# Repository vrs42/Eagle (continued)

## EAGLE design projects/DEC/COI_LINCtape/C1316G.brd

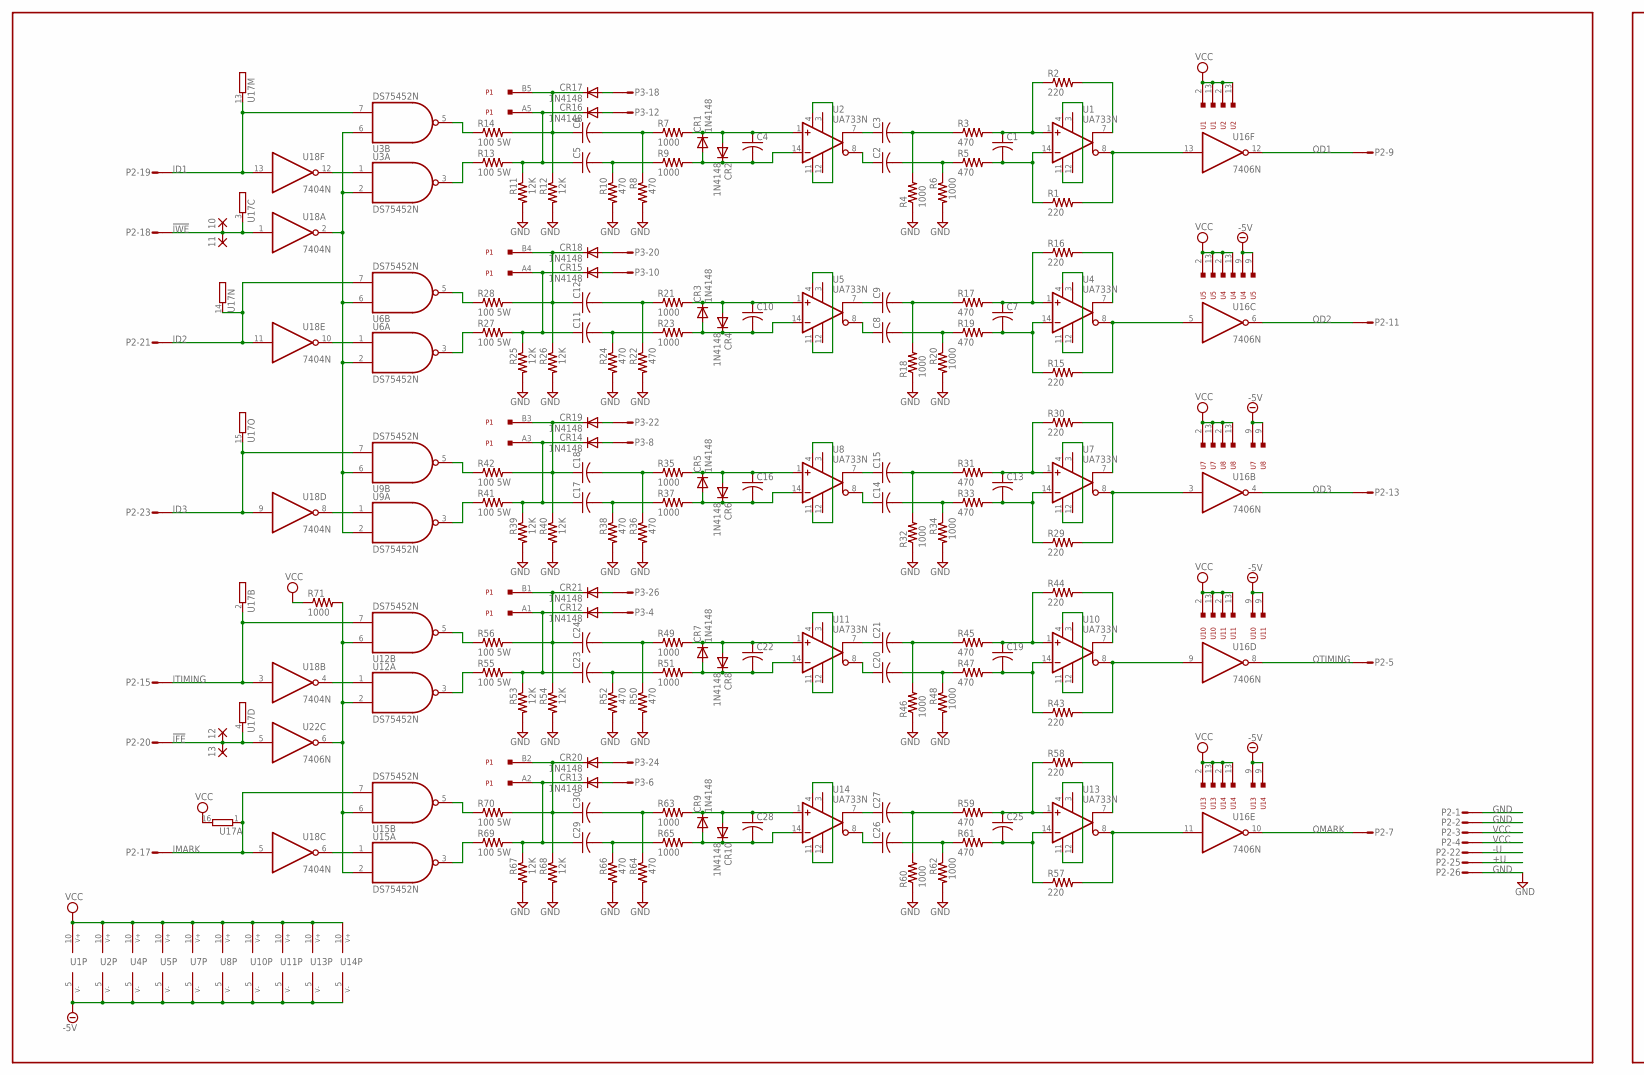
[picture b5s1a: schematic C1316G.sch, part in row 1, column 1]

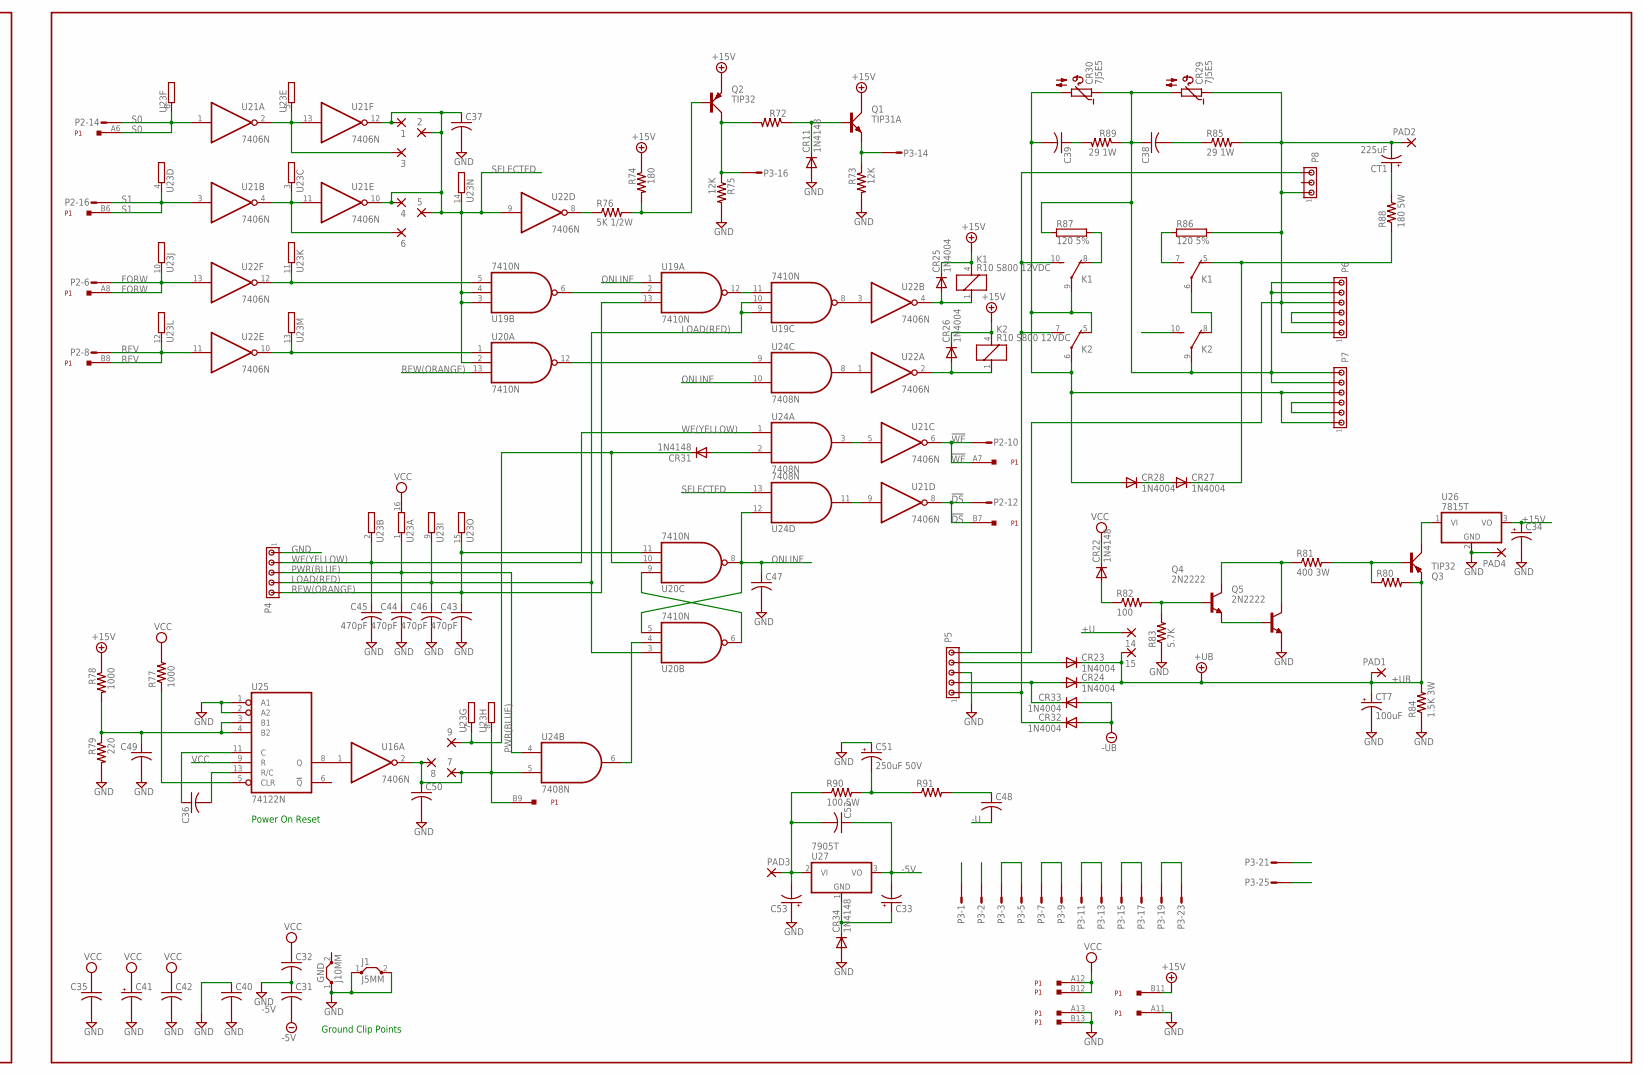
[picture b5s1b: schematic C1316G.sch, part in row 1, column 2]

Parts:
1, 2, 3, 4, 5, 6, 7, 8, 9, 10, 11, 12, 13, 14, 15: 1,6/0,8
C1, C4, C7, C10, C13, C16, C19, C22, C25, C28, C50: C-US102-043X133; C102-043X133
C2, C3, C5, C6, C8, C9, C11, C12, C14, C15, C17, C18, C20, C21, C23, C24, C26, C27, C29, C30, C31, C32, C35, C36, C37, C40, C42, C47, C48, C49, C52: C-US050-025X075; C050-025X075
C33, C34: CPOL-USB45181B; B45181B
C38, C39: C-US150-054X183; C150-054X183
C41, C53: CPOL-USE22-6AXIAL; E22-6
C43, C44, C45, C46: 470pF; C050-025X075
C51: 250uF 50V; E35-12
CR1, CR2, CR3, CR4, CR5, CR6, CR7, CR8, CR9, CR10, CR11, CR12, CR13, CR14, CR15, CR16, CR17, CR18, CR19, CR20, CR21, CR22, CR31, CR34: 1N4148; DO35-10
CR23, CR24, CR25, CR26, CR27, CR28, CR32, CR33: 1N4004; DO41-10
CR29, CR30: 7J5E5; N644B
CT1: 225uF; E55-25
CT7: 100uF; E55-25
GND: J10MM; 10
J1: J5MM; 05
K1, K2: R10 S800 12VDC; R10
P1: EDGE13X2
P2: 26HS; 26H
P3: 26VS; 26V
P4, P5: MTA05-156; 1X5MTA
P6, P7: MTA06-156; 1X6MTA
P8: MTA03-156; 1X3MTA
PAD1, PAD2: 3,81/1,1
PAD3, PAD4: 1,6/0,8
Q1: TIP31A; TO220AV
Q2, Q3: TIP32; TO220AV
Q4, Q5: 2N2222; TO5
R1, R2, R15, R16, R29, R30, R43, R44, R57, R58, R79: 220; 0207/10
R3, R5, R8, R10, R17, R19, R22, R24, R31, R33, R36, R38, R45, R47, R50, R52, R59, R61, R64, R66: 470; 0207/10
R4, R6, R7, R9, R18, R20, R21, R23, R32, R34, R35, R37, R46, R48, R49, R51, R60, R62, R63, R65, R71, R77, R78: 1000; 0207/10
R11, R12, R25, R26, R39, R40, R53, R54, R67, R68, R73, R75: 12K; 0207/10
R13, R14, R27, R28, R41, R42, R55, R56, R69, R70, R90: 100 5W; 0414/20
R72, R80, R91: R-US_0207/10; 0207/10
R74: 180; 0207/10
R76: 5K 1/2W; 0411/15
R81: 400 3W; 0617/22
R82: 100; 0207/10
R83: 5.7K; 0207/10
R84: 1.5K 3W; 0414/20
R85, R89: 29 1W; 0411/15
R86, R87: 120 5%; KH216-8
R88: 180 5W; 0414/20
U1, U2, U4, U5, U7, U8, U10, U11, U13, U14: UA733N; DIL14
U3, U6, U9, U12, U15: DS75452N; DIL08
U16, U21, U22: 7406N; DIL14
U17, U23: E15R; DIL16
U18: 7404N; DIL14
U19, U20: 7410N; DIL14
U24: 7408N; DIL14
U25: 74122N; DIL14
U26: 7815T; TO220H
U27: 7905T; TO220H

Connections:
!DS: P1.B7, P2.12, U21.8 (O)
!IFE: 12.1, 13.1, P2.20, U17.4 (1), U22.5 (I)
!IWE: 10.1, 11.1, P2.18, U17.3 (1), U18.1 (I)
!WE: P1.A7, P2.10, U21.6 (O)
+15V: C34.+, CR25.C, CR26.C, K1.4 (7), K2.4 (7), P1.B11, Q1.C, Q2.E, R74.1, R78.1, U26.3 (VO)
+U: 14.1, P2.25
+UB: 15.1, CR23.C, CR24.C, CT7.+, PAD1.1, Q3.E, R80.2, R84.2
-5V: C31.2, C33.-, C52.1, U1.5 (V-), U2.5 (V-), U4.5 (V-), U4.9, U5.5 (V-), U5.9, U7.5 (V-), U7.9, U8.5 (V-), U8.9, U10.5 (V-), U10.9, U11.5 (V-), U11.9, U13.5 (V-), U13.9, U14.5 (V-), U14.9, U27.3 (VO)
-U: C48.2, P2.22
-UB: CR32.A, CR33.A
FORW: P1.A8, P2.6, U22.13 (I), U23.10 (1)
GND: C31.1, C32.2, C34.-, C35.2, C37.2, C40.1, C40.2, C41.-, C42.2, C43.2, C44.2, C45.2, C46.2, C47.2, C49.2, C50.2, C51.+, C53.+, CR11.A, CR34.A, CT7.-, GND.1, J1.1, J1.2, P1.A11, P1.A13, P1.B13, P2.1, P2.2, P2.26, P4.1, P5.3, PAD4.1, Q5.1 (E), R4.1, R6.2, R8.2, R10.2, R11.2, R12.2, R18.1, R20.2, R22.2, R24.2, R25.2, R26.2, R32.1, R34.2, R36.2, R38.2, R39.2, R40.2, R46.1, R48.2, R50.2, R52.2, R53.2, R54.2, R60.1, R62.2, R64.2, R66.2, R67.2, R68.2, R73.2, R75.2, R79.2, R83.1, R84.1, U3.4 (GND), U6.4 (GND), U9.4 (GND), U12.4 (GND), U15.4 (GND), U16.7 (GND), U18.7 (GND), U19.7 (GND), U20.7 (GND), U21.7 (GND), U22.7 (GND), U24.7 (GND), U25.1 (A1), U25.2 (A2), U25.7 (GND), U26.2 (GND)
ID1: P2.19, U3.7 (I1), U17.13 (1), U18.13 (I)
ID2: P2.21, U6.7 (I1), U17.14 (1), U18.11 (I)
ID3: P2.23, U9.7 (I1), U17.15 (1), U18.9 (I)
IMARK: P2.17, U15.7 (I1), U17.1, U18.5 (I)
ITIMING: P2.15, U12.7 (I1), U17.2 (1), U18.3 (I)
K1: CR25.A, K1.1, U22.4 (O)
K2: CR26.A, K2.1, U22.2 (O)
LOAD(RED): C46.1, P4.4, U19.9 (I0), U19.10 (I1), U20.3 (I0), U23.9 (1)
unnamed: C13.2, R29.1, R33.2, U7.14 (-IN)
unnamed: R29.2, U7.8 (OUT-), U16.3 (I)
unnamed: C13.1, R30.1, R31.2, U7.1 (+IN)
unnamed: R30.2, U7.7 (OUT+)
unnamed: C15.2, R31.1, R32.2
unnamed: C14.2, R33.1, R34.1
unnamed: C16.1, CR5.C, CR6.A, R35.2, U8.1 (+IN)
unnamed: C17.2, R37.1, R38.1
unnamed: C16.2, CR5.A, CR6.C, R37.2, U8.14 (-IN)
unnamed: R41.1, U9.3 (O)
unnamed: C1.2, R1.1, R5.2, U1.14 (-IN)
unnamed: R1.2, U1.8 (OUT-), U16.13 (I)
unnamed: C1.1, R2.1, R3.2, U1.1 (+IN)
unnamed: R2.2, U1.7 (OUT+)
unnamed: C6.2, R7.1, R8.1
unnamed: C3.2, R3.1, R4.2
unnamed: U21.9 (I), U24.11 (O)
unnamed: C6.1, CR17.C, P1.B5, R12.1, R14.2
unnamed: C2.2, R5.1, R6.1
unnamed: C5.1, CR16.C, P1.A5, R11.1, R13.2
unnamed: CR32.C, K1.10 (S), K2.7 (S), P5.1, P8.3
unnamed: CR29.1, CT1.-, P5.5, P6.1, P6.4, P8.1, PAD2.1, R85.2, R86.2
unnamed: C4.1, CR1.C, CR2.A, R7.2, U2.1 (+IN)
unnamed: CR23.A, P5.4
unnamed: C7.2, R15.1, R19.2, U4.14 (-IN)
unnamed: CR24.A, CR33.C, P5.2
unnamed: C5.2, R9.1, R10.1
unnamed: C4.2, CR1.A, CR2.C, R9.2, U2.14 (-IN)
unnamed: R15.2, U4.8 (OUT-), U16.5 (I)
unnamed: C7.1, R16.1, R17.2, U4.1 (+IN)
unnamed: R16.2, U4.7 (OUT+)
unnamed: Q2.B, R74.2, R76.2
unnamed: C9.2, R17.1, R18.2
unnamed: R13.1, U3.3 (O)
unnamed: R14.1, U3.5 (O)
unnamed: C8.2, R19.1, R20.1
unnamed: C10.1, CR3.C, CR4.A, R21.2, U5.1 (+IN)
unnamed: C11.2, R23.1, R24.1
unnamed: C10.2, CR3.A, CR4.C, R23.2, U5.14 (-IN)
unnamed: R27.1, U6.3 (O)
unnamed: U1.4 (GA1), U1.11 (GB1)
unnamed: R28.1, U6.5 (O)
unnamed: U4.4 (GA1), U4.11 (GB1)
unnamed: U5.4 (GA1), U5.11 (GB1)
unnamed: C9.1, U5.7 (OUT+)
unnamed: C8.1, U5.8 (OUT-)
unnamed: U3.2 (I1), U3.6 (I0), U6.2 (I1), U6.6 (I0), U9.2 (I1), U9.6 (I0), U18.2 (O)
unnamed: U6.1 (I0), U18.10 (O)
unnamed: U2.4 (GA1), U2.11 (GB1)
unnamed: C12.2, R21.1, R22.1
unnamed: C11.1, CR15.C, P1.A4, R25.1, R27.2
unnamed: C12.1, CR18.C, P1.B4, R26.1, R28.2
unnamed: C3.1, U2.7 (OUT+)
unnamed: C2.1, U2.8 (OUT-)
unnamed: C23.1, CR12.C, P1.A1, R53.1, R55.2
unnamed: U3.1 (I0), U18.12 (O)
unnamed: P3.3, P3.5
unnamed: CR12.A, P3.4
unnamed: R42.1, U9.5 (O)
unnamed: CR13.A, P3.6
unnamed: R43.2, U10.8 (OUT-), U16.9 (I)
unnamed: R57.2, U13.8 (OUT-), U16.11 (I)
unnamed: U7.4 (GA1), U7.11 (GB1)
unnamed: U8.4 (GA1), U8.11 (GB1)
unnamed: U12.1 (I0), U18.4 (O)
unnamed: U15.1 (I0), U18.6 (O)
unnamed: U9.1 (I0), U18.8 (O)
unnamed: P3.7, P3.9
unnamed: CR14.A, P3.8
unnamed: Q4.3 (C), Q5.3 (C), R81.1
unnamed: CR15.A, P3.10
unnamed: 7.1, 8.1, C50.1, P1.B9, U16.2 (O), U23.8 (1), U24.5 (I1)
unnamed: P3.11, P3.13
unnamed: CR16.A, P3.12
unnamed: CR11.C, Q1.B, R72.1
unnamed: P3.14, Q1.E, R73.1
unnamed: C15.1, U8.7 (OUT+)
unnamed: C14.1, U8.8 (OUT-)
unnamed: R76.1, U22.8 (O)
unnamed: 6.1, U21.4 (O), U21.11 (I), U23.3 (1)
unnamed: C18.2, R35.1, R36.1
unnamed: C17.1, CR14.C, P1.A3, R39.1, R41.2
unnamed: C18.1, CR19.C, P1.B3, R40.1, R42.2
unnamed: C39.1, R89.2
unnamed: C19.2, R43.1, R47.2, U10.14 (-IN)
unnamed: P3.15, P3.17
unnamed: C19.1, R44.1, R45.2, U10.1 (+IN)
unnamed: R44.2, U10.7 (OUT+)
unnamed: C21.2, R45.1, R46.2
unnamed: C20.2, R47.1, R48.1
unnamed: C22.1, CR7.C, CR8.A, R49.2, U11.1 (+IN)
unnamed: C23.2, R51.1, R52.1
unnamed: C22.2, CR7.A, CR8.C, R51.2, U11.14 (-IN)
unnamed: R55.1, U12.3 (O)
unnamed: R56.1, U12.5 (O)
unnamed: U10.4 (GA1), U10.11 (GB1)
unnamed: U11.4 (GA1), U11.11 (GB1)
unnamed: C21.1, U11.7 (OUT+)
unnamed: C20.1, U11.8 (OUT-)
unnamed: R71.2, U12.2 (I1), U12.6 (I0), U15.2 (I1), U15.6 (I0), U22.6 (O)
unnamed: U21.5 (I), U24.3 (O)
unnamed: U19.8 (O), U22.3 (I)
unnamed: C24.2, R49.1, R50.1
unnamed: C48.1, R91.2
unnamed: C24.1, CR21.C, P1.B1, R54.1, R56.2
unnamed: 3.1, U21.2 (O), U21.13 (I), U23.5 (1)
unnamed: C25.2, R57.1, R61.2, U13.14 (-IN)
unnamed: P3.16, Q2.C, R72.2, R75.1
unnamed: C25.1, R58.1, R59.2, U13.1 (+IN)
unnamed: R58.2, U13.7 (OUT+)
unnamed: C27.2, R59.1, R60.2
unnamed: C26.2, R61.1, R62.1
unnamed: C28.1, CR9.C, CR10.A, R63.2, U14.1 (+IN)
unnamed: C29.2, R65.1, R66.1
unnamed: C28.2, CR9.A, CR10.C, R65.2, U14.14 (-IN)
unnamed: R69.1, U15.3 (O)
unnamed: R70.1, U15.5 (O)
unnamed: U13.4 (GA1), U13.11 (GB1)
unnamed: U14.4 (GA1), U14.11 (GB1)
unnamed: C27.1, U14.7 (OUT+)
unnamed: C26.1, U14.8 (OUT-)
unnamed: C38.1, CR29.2, CR30.1, K2.9, P6.5, P6.6, P7.5, P7.6, R87.1, R89.1
unnamed: C30.2, R63.1, R64.1
unnamed: C29.1, CR13.C, P1.A2, R67.1, R69.2
unnamed: C30.1, CR20.C, P1.B2, R68.1, R70.2
unnamed: U19.5 (I2), U22.12 (O), U23.11 (1)
unnamed: U22.1 (I), U24.8 (O)
unnamed: 9.1, CR31.C, U20.10 (I1), U23.7 (1)
unnamed: C33.+, CR34.C, U27.1 (GND)
unnamed: U20.1 (I0), U22.10 (O), U23.13 (1)
unnamed: CR19.A, P3.22
unnamed: C52.2, C53.-, PAD3.1, R90.1, U27.2 (VI)
unnamed: Q3.C, U26.1 (VI)
unnamed: Q3.B, R80.1, R81.2
unnamed: U19.2 (I1), U19.6 (O)
unnamed: Q4.1 (E), Q5.2 (B)
unnamed: Q4.2 (B), R82.2, R83.2
unnamed: C51.-, R90.2, R91.1
unnamed: C38.2, R85.1
unnamed: U19.11 (I2), U19.12 (O)
unnamed: U20.12 (O), U24.9 (I0)
unnamed: U20.4 (I1), U24.6 (O)
unnamed: CR27.C, K1.5 (O), R88.1
unnamed: U20.6 (O), U20.9 (I0)
unnamed: C49.1, R78.2, R79.1, U25.3 (B1), U25.4 (B2)
unnamed: CR22.A, R82.1
unnamed: C39.2, CR28.A, CR30.2, K1.9, K2.5 (O), K2.6, P7.1, P7.4
unnamed: K1.7 (S), R86.1
unnamed: CR31.A, U24.2 (I1)
unnamed: C36.2, U25.13 (R/C)
unnamed: C36.1, U25.11 (C)
unnamed: R77.1, U25.5 (CLR)
unnamed: U16.1 (I), U25.8 (Q)
unnamed: P6.2, P6.3
unnamed: P7.2, P7.3
unnamed: P3.19, P3.23
unnamed: CR20.A, P3.24
unnamed: CR21.A, P3.26
unnamed: CR17.A, P3.18
unnamed: CR18.A, P3.20
unnamed: K1.8 (O), R87.2
unnamed: CT1.+, R88.2
unnamed: CR27.A, CR28.C
unnamed: K1.6, K2.8 (O)
OD1: P2.9, U16.12 (O)
OD2: P2.11, U16.6 (O)
OD3: P2.13, U16.4 (O)
OMARK: P2.7, U16.10 (O)
ONLINE: C47.1, U19.1 (I0), U20.5 (I2), U20.8 (O), U24.10 (I1), U24.12 (I0)
OTIMING: P2.5, U16.8 (O)
PWR(BLUE): C44.1, P4.3, U23.1, U24.4 (I0)
REV: P1.B8, P2.8, U22.11 (I), U23.12 (1)
REW(ORANGE): C43.1, P4.5, U19.13 (I2), U20.11 (I2), U20.13 (I2), U23.15 (1)
S0: P1.A6, P2.14, U21.1 (I), U23.6 (1)
S1: P1.B6, P2.16, U21.3 (I), U23.4 (1)
SELECTED: 1.1, 2.1, 4.1, 5.1, C37.1, U19.3 (I0), U19.4 (I1), U20.2 (I1), U21.10 (O), U21.12 (O), U22.9 (I), U23.14 (1), U24.13 (I1)
VCC: C32.1, C35.1, C41.+, C42.1, CR22.C, P1.A12, P1.B12, P2.3, P2.4, R71.1, R77.2, U1.2, U1.10 (V+), U1.13, U2.2, U2.10 (V+), U2.13, U3.8 (VCC), U4.2, U4.10 (V+), U4.13, U5.2, U5.10 (V+), U5.13, U6.8 (VCC), U7.2, U7.10 (V+), U7.13, U8.2, U8.10 (V+), U8.13, U9.8 (VCC), U10.2, U10.10 (V+), U10.13, U11.2, U11.10 (V+), U11.13, U12.8 (VCC), U13.2, U13.10 (V+), U13.13, U14.2, U14.10 (V+), U14.13, U15.8 (VCC), U16.14 (VCC), U17.16 (2), U18.14 (VCC), U19.14 (VCC), U20.14 (VCC), U21.14 (VCC), U22.14 (VCC), U23.16 (2), U24.14 (VCC), U25.9 (R), U25.14 (VCC)
WE(YELLOW): C45.1, P4.2, U23.2 (1), U24.1 (I0)

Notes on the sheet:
Power On Reset
Ground Clip Points

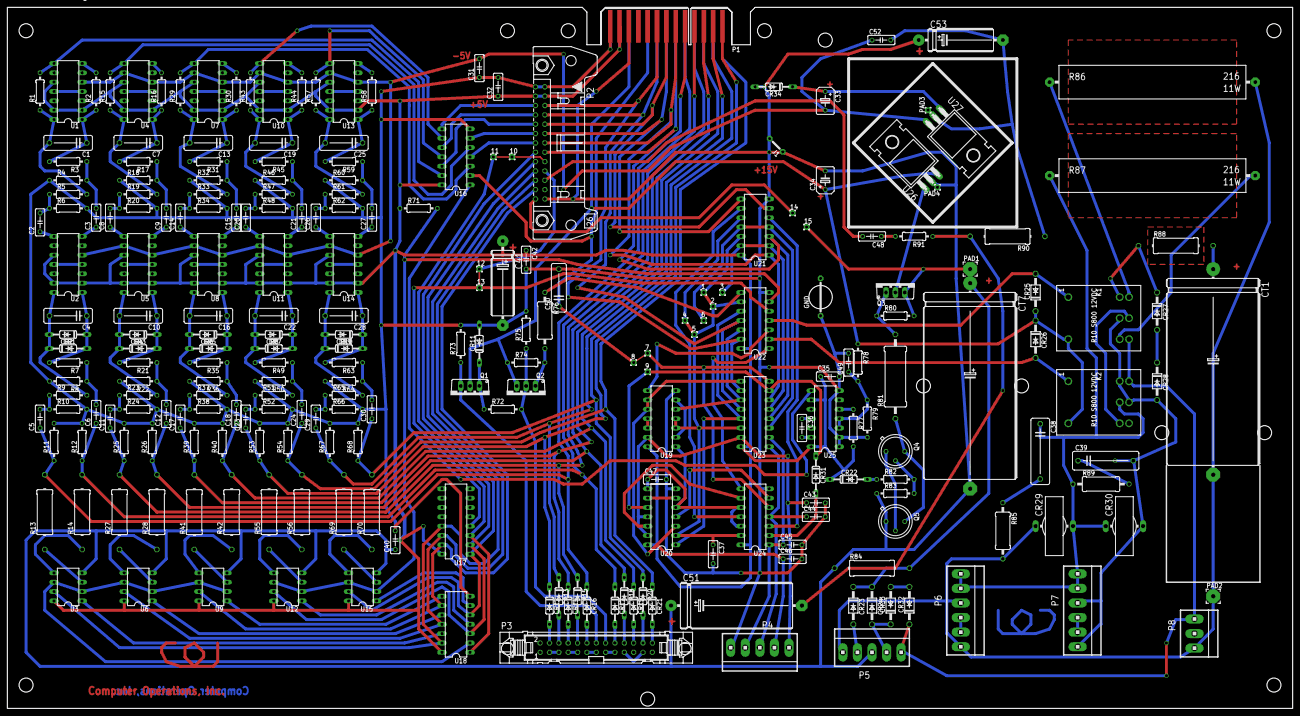
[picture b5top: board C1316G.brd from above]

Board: 2 copper layers, 349.2 x 190.5 mm, 243 parts (0 on the bottom side), 198 nets.
